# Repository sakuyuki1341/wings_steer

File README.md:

# wings_steer

"wings_steer" is a system of steering in U.E.C.wings.

# DEMO

No information.(Additional information will come soon.)

# Features

to use Arduino in this system.
Befor we use Renesas, but now we use it to takeover.

# Requirement

No information.(Additional information will come soon.)

# Installation

No information.(Additional information will come soon.)

# Usage

No information.(Additional information will come soon.)

# Note

No informa

# Author

* Sakuyuki
* U.E.C.wings
* y1810678@gmail.com

# License

"wings_steer" is under [MIT license](https://en.wikipedia.org/wiki/MIT_License).

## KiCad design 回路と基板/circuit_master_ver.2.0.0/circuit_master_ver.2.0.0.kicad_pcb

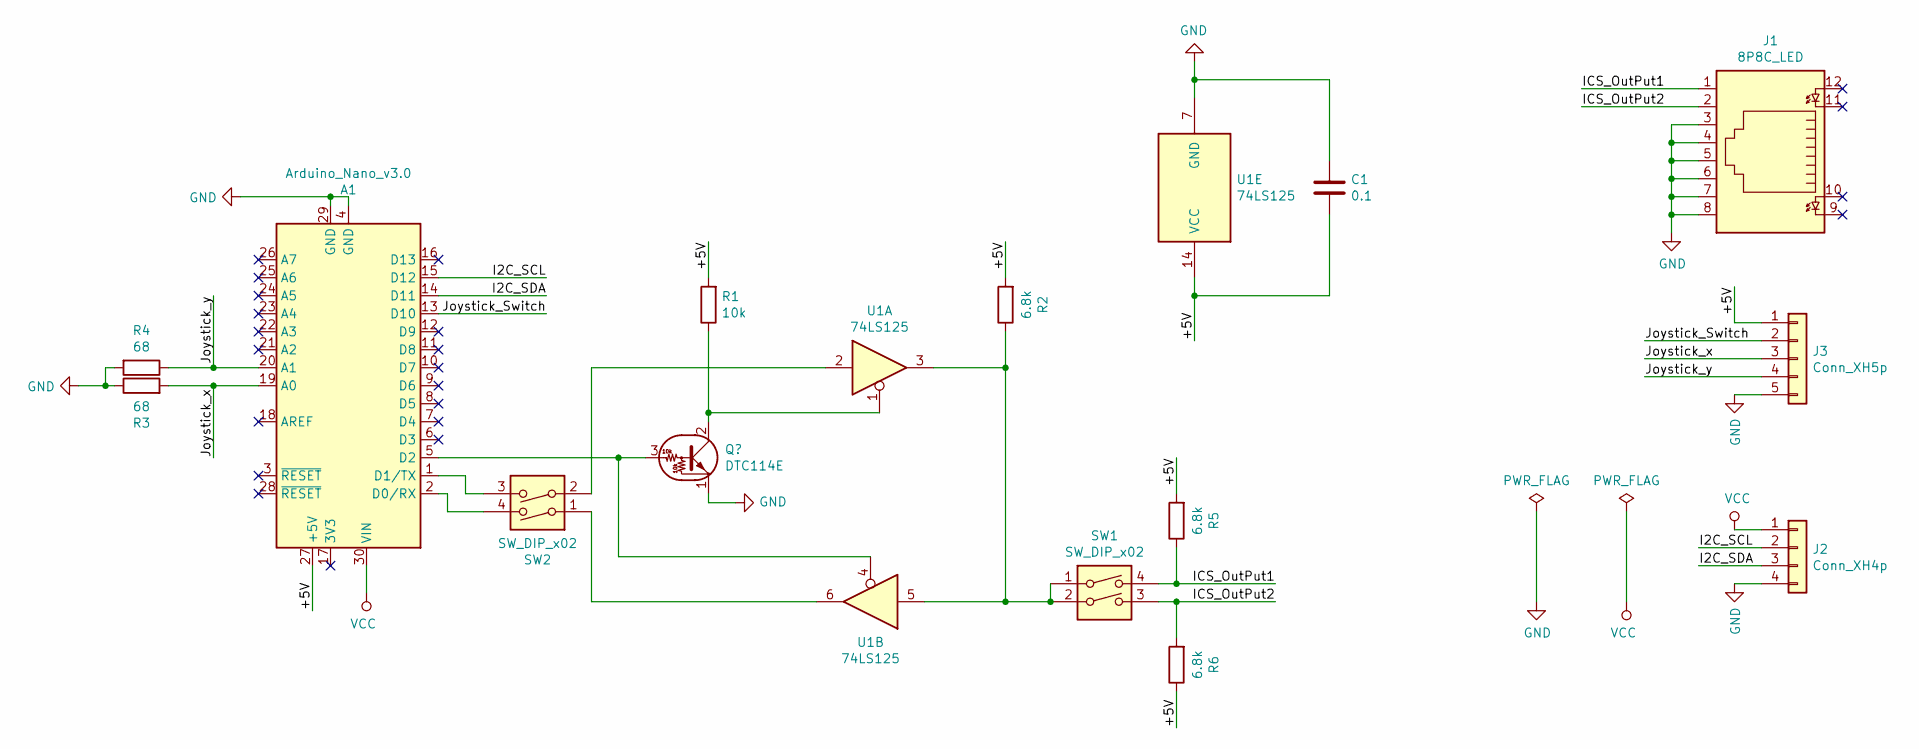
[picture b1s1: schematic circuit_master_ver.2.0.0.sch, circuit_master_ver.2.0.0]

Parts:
A1: Arduino_Nano_v3.0; Arduino_Nano
C1: 0.1; C_Disc_D4.7mm_W2.5mm_P5.00mm
J1: 8P8C_LED; RJ45_Cetus_J1B1211CCD_Horizontal
J2: Conn_XH4p; JST_XH_B4B-XH-A_1x04_P2.50mm_Vertical
J3: Conn_XH5p; JST_XH_B5B-XH-A_1x05_P2.50mm_Vertical
R1: 10k; R_Axial_DIN0207_L6.3mm_D2.5mm_P10.16mm_Horizontal
R2, R5, R6: 6.8k; R_Axial_DIN0207_L6.3mm_D2.5mm_P10.16mm_Horizontal
R3, R4: 68; R_Axial_DIN0207_L6.3mm_D2.5mm_P10.16mm_Horizontal
SW1, SW2: SW_DIP_x02; SW_DIP_SPSTx02_Slide_9.78x7.26mm_W7.62mm_P2.54mm
U1: 74LS125; DIP-14_W7.62mm_Socket_LongPads

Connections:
/+5V: A1.27 (+5V), C1.2, J3.1, R1.2, R2.2, R5.2, R6.1, U1.14 (VCC)
/I2C_SCL: A1.15 (D12), J2.2
/I2C_SDA: A1.14 (D11), J2.3
/ICS_OutPut1: J1.1, R5.1, SW1.4
/ICS_OutPut2: J1.2, R6.2, SW1.3
/Joystick_Switch: A1.13 (D10), J3.2
/Joystick_x: A1.19 (A0), J3.3, R3.2
/Joystick_y: A1.20 (A1), J3.4, R4.1
GND: A1.4 (GND), A1.29 (GND), C1.1, J1.3, J1.4, J1.5, J1.6, J1.7, J1.8, J2.4, J3.5, R3.1, R4.2, U1.7 (GND); also elsewhere on the board
unnamed: A1.1 (D1/TX), SW2.3
unnamed: A1.2 (D0/RX), SW2.4
unnamed 11: A1.5 (D2), U1.4; also elsewhere on the board
unnamed 12: R1.1, U1.1; also elsewhere on the board
unnamed: R2.1, SW1.1, SW1.2, U1.3, U1.5
unnamed: SW2.1, U1.6
unnamed: SW2.2, U1.2
VCC: A1.30 (VIN), J2.1

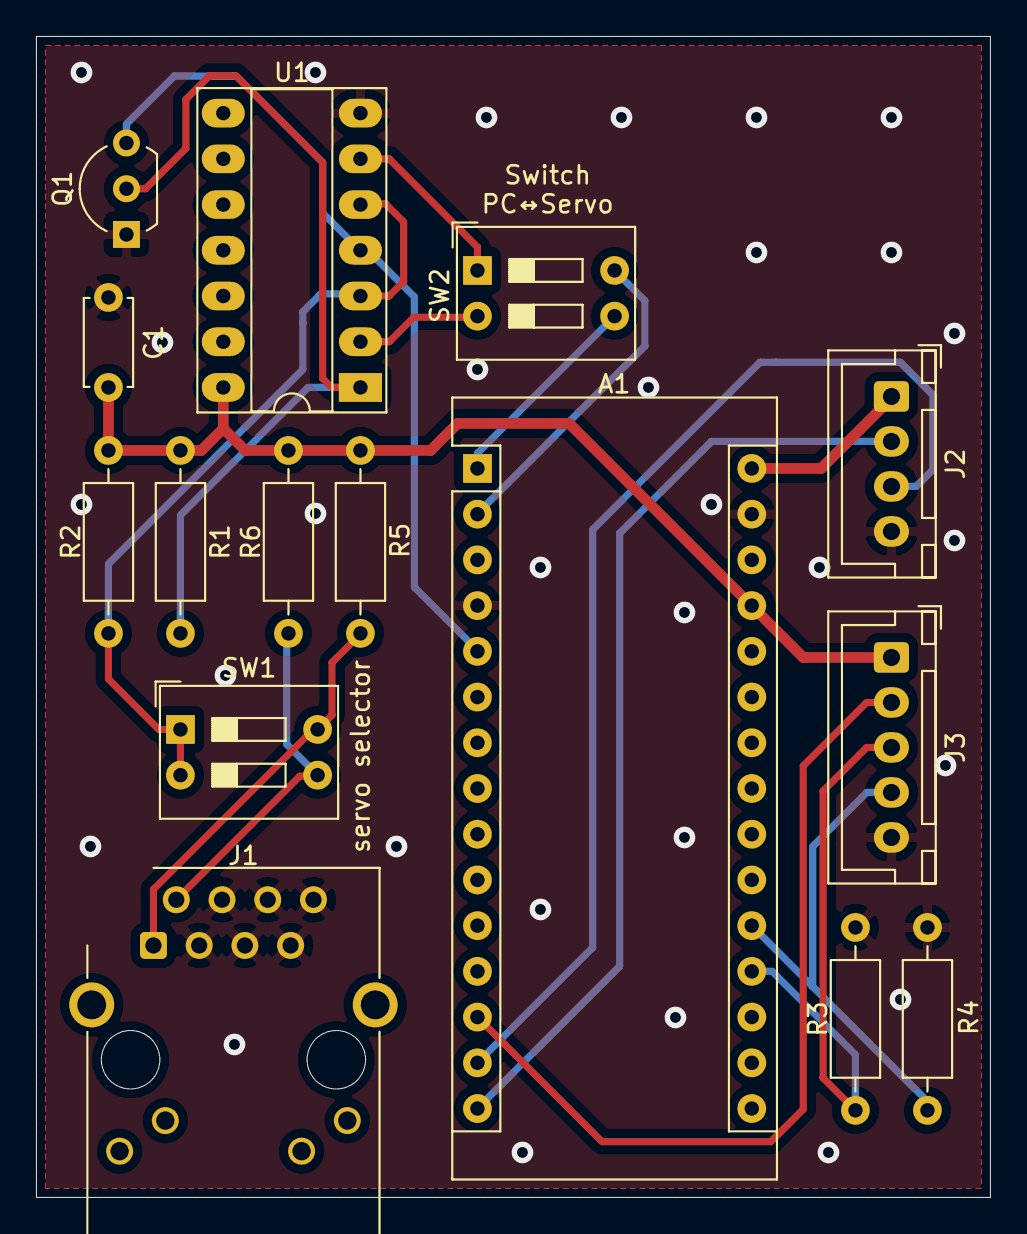
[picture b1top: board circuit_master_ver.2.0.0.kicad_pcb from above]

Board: 2 copper layers, 53.0 x 64.5 mm, 15 parts (0 on the bottom side), 17 nets.

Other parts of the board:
Q1: DTC114EL; TO-92L_Inline_Wide

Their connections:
GND: Q1.1; also elsewhere on the board
unnamed 11: Q1.3; also elsewhere on the board
unnamed 12: Q1.2; also elsewhere on the board

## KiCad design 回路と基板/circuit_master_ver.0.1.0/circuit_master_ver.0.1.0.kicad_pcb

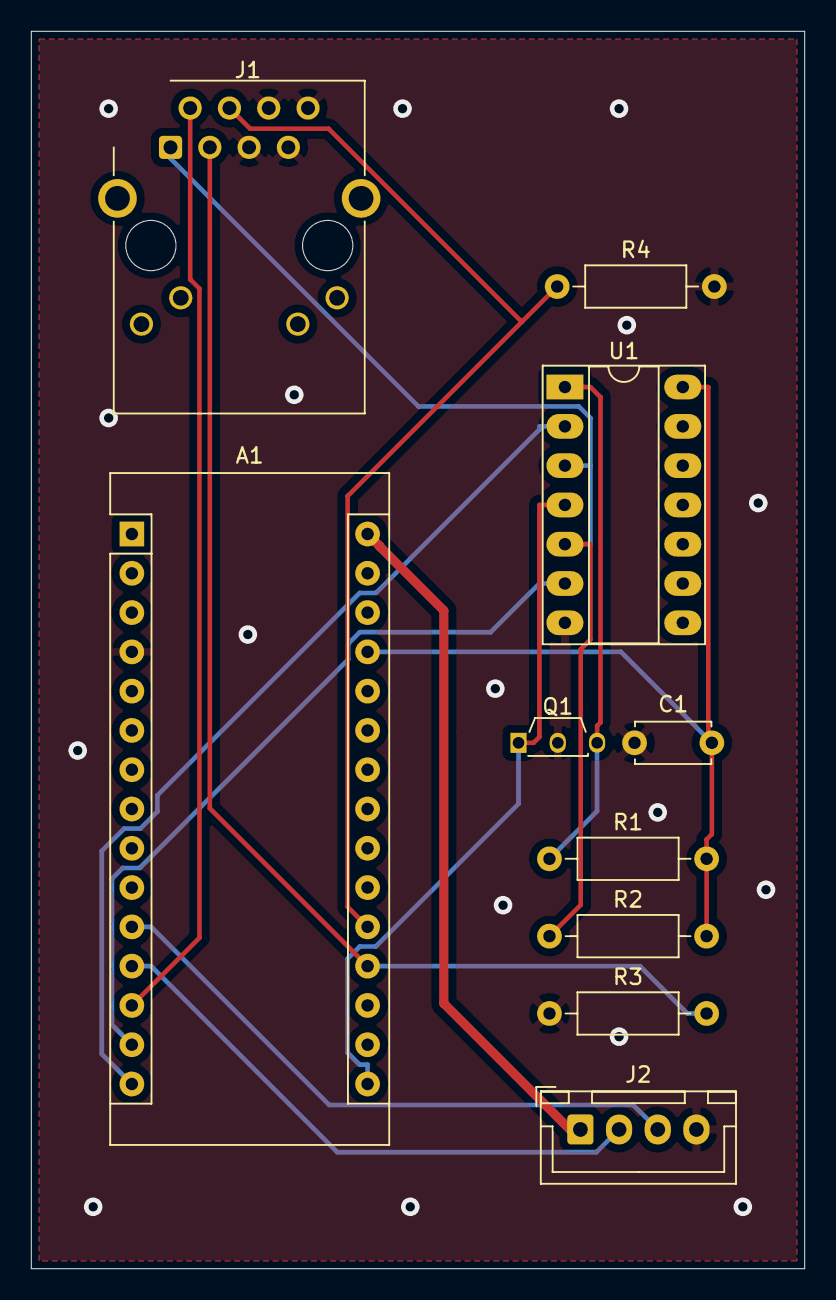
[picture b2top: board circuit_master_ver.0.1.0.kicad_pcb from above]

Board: 2 copper layers, 50.0 x 80.0 mm, 10 parts (0 on the bottom side), 13 nets.

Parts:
A1: Arduino_Nano_v3.0; Arduino_Nano
C1: 0.1; C_Disc_D4.7mm_W2.5mm_P5.00mm
J1: 8P8C_LED; RJ45_Cetus_J1B1211CCD_Horizontal
J2: Conn_XH4p; JST_XH_B4B-XH-A_1x04_P2.50mm_Vertical
Q1: DTC114EL; TO-92S_Wide
R1: 10k; R_Axial_DIN0207_L6.3mm_D2.5mm_P10.16mm_Horizontal
R2: 2.2k; R_Axial_DIN0207_L6.3mm_D2.5mm_P10.16mm_Horizontal
R3, R4: 68; R_Axial_DIN0207_L6.3mm_D2.5mm_P10.16mm_Horizontal
U1: 74LS125; DIP-14_W7.62mm_Socket_LongPads

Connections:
/+5V: A1.27, C1.2, R1.2, R2.2, U1.14
/I2C_SCL: A1.12, J2.2
/I2C_SDA: A1.11, J2.3
/ICS_OutPut: J1.1, R2.1, U1.3, U1.5
/Joystick_Switch: A1.13, J1.2
/Joystick_x: A1.19, J1.3, R3.2
/Joystick_y: A1.20, J1.4, R4.1
GND: A1.4, A1.29, C1.1, J1.5, J1.6, J1.7, J1.8, J2.4, Q1.2, R3.1, R4.2, U1.7
unnamed: A1.14, U1.6
unnamed: A1.15, U1.2
unnamed: A1.16, Q1.1, U1.4
unnamed: Q1.3, R1.1, U1.1
VCC: A1.30, J2.1

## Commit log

2020-09-06 upload befor we create
2020-09-06 softwareSerialの動作テスト実行
2020-09-08 SoftwareSerialを用いたコマンドラインの作成完了
2020-09-08 とりあえずスティックで動いてデバッグモードも動作できるver.0.2を作成しました。
2020-09-08 誤字訂正
2020-09-09 ver1.0作成開始
2020-09-10 アナログスティックの入力などから、サーボモータへ送信する値の算出計算の完成
2020-09-10 操舵のソースコード。及び引き継ぎ出力
2020-09-13 資料更新
